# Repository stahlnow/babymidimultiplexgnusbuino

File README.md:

babymidimultiplexgnusbuino
==========================

An 8-channel MIDI controller board based on Babymidignusbuino

See http://wiki.sgmk-ssam.ch/index.php?title=Babymidimultiplexgnusbuino

See https://github.com/mirdej/babygnusbuino

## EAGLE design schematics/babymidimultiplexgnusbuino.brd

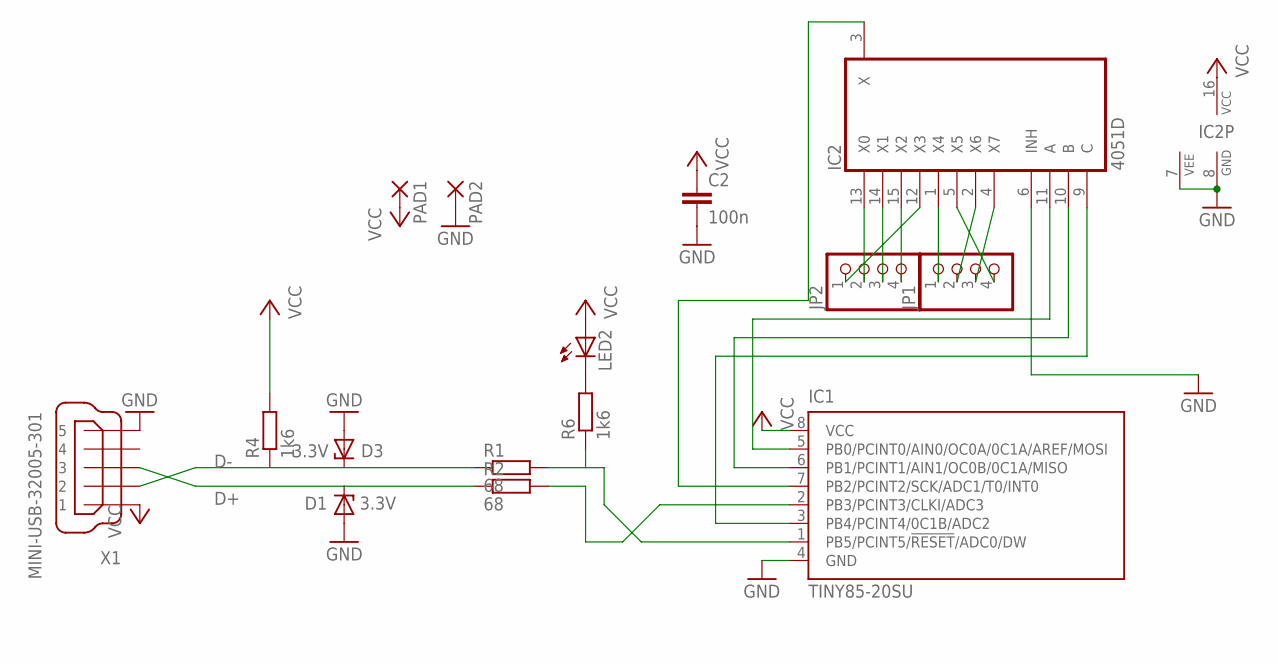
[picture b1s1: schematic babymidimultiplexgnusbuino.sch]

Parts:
C2: 100n; C0603
D1, D3: 3.3V; SOD80C
IC1: TINY85-20SU; 8S2; MPN ATTINY13-20SU
IC2: 4051D; SO16
JP1, JP2: PINHD-1X4; 1X04
LED2: LEDKA-3528ASYC; KA-3528ASYC
PAD1, PAD2: SMD5; SMD2,54-5,08
R1, R2: 68; R1206
R4, R6: 1k6; R1206
X1: MINI-USB-32005-301; 32005-301

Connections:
D+: D1.C, R2.1, X1.3
D-: D3.C, R1.1, R4.1, X1.2
GND: C2.2, D1.A, D3.A, IC1.4 (GND), IC2.6 (INH), IC2.7 (VEE), IC2.8 (GND), PAD2.1, X1.5
unnamed: IC1.2 (PB3/PCINT3/CLKI/ADC3), R2.2
unnamed: IC1.1 (PB5/PCINT5/!RESET!/ADC0/DW), R1.2, R6.1
unnamed: IC1.7 (PB2/PCINT2/SCK/ADC1/T0/INT0), IC2.3 (X)
unnamed: IC1.6 (PB1/PCINT1/AIN1/OC0B/0C1A/MISO), IC2.10 (B)
unnamed: IC1.5 (PB0/PCINT0/AIN0/OC0A/0C1A/AREF/MOSI), IC2.11 (A)
unnamed: IC1.3 (PB4/PCINT4/0C1B/ADC2), IC2.9 (C)
unnamed: LED2.C, R6.2
unnamed: IC2.1 (X4), JP1.1
unnamed: IC2.2 (X6), JP1.2
unnamed: IC2.4 (X7), JP1.3
unnamed: IC2.5 (X5), JP1.4
unnamed: IC2.12 (X3), JP2.1
unnamed: IC2.13 (X0), JP2.2
unnamed: IC2.14 (X1), JP2.3
unnamed: IC2.15 (X2), JP2.4
VCC: C2.1, IC1.8 (VCC), IC2.16 (VCC), LED2.A, PAD1.1, R4.2, X1.1

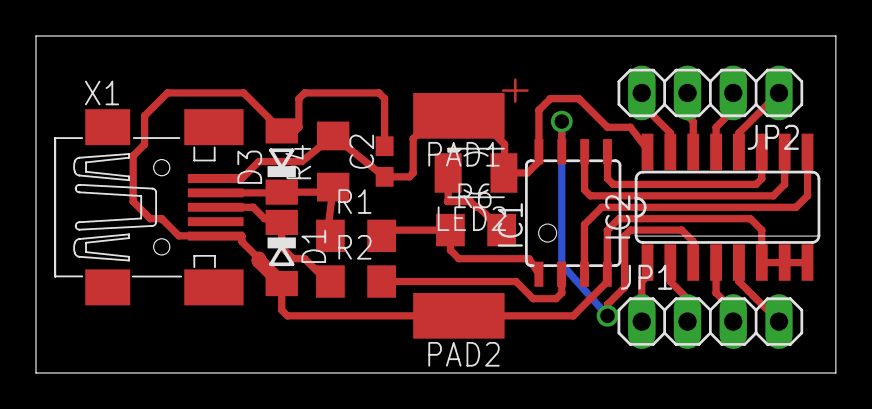
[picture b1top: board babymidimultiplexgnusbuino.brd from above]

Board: 2 copper layers, 44.4 x 18.7 mm, 15 parts (0 on the bottom side), 19 nets.

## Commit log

2014-07-29 source code + schematics
2014-09-14 added .gitignore
2014-09-14 bug fix
